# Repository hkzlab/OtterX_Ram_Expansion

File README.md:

# OtterX RAM Expansion

## Introduction

This card expands the RAM of your [OtterX](https://www.tindie.com/products/wavicle/otterx-8-bit-retro-computer/) (a DIY CommanderX16 compatible) computer to 2MB!

Once You switch [J27](https://github.com/RetroRemake/OtterX_Assembly/blob/main/OtterX%20Schematics.pdf) to enable the external RAM and install this board, the computer will automatically detect the 2MB.

### Disclaimer

I take NO responsibility for what happens if you decide to build and use this card. Your computer might crash, catch fire or be destroyed in other nasty ways.
You're encourauged to take what you deem fit from this, and use it in your projects!

## Known Issues

### Rev. 0

- None

## Bill of Materials

| Component         | Qty | Type / Value           | Link                                                     |
| ----------------- | --- | ---------------------- | -------------------------------------------------------- |
| C1, C2, C3, C4    |  4  | 100nF / 1206 / ceramic | https://www.mouser.it/ProductDetail/581-1206YC104JAT2A   |
| U4                |  1  | 74AC139 / SOIC-16      | https://www.mouser.it/ProductDetail/863-MC74AC139DR2G    |
| U1, U2, U3        |  3  | 512Kx8 SRAM / SOP-32   | https://www.mouser.it/ProductDetail/968-R1LP0408DSP5SIS1 |
| J1                |  1  | 2x20 header, 2mm pitch | https://www.mouser.it/ProductDetail/200-MTMM12004TD157 or https://www.mouser.it/ProductDetail/200-MTMM12009LD350 |

Depending on whether you added or not a socket for the IC in the area where the expansion is installed, select one type of header or the other: `MTMM-120-09-L-D-350` clears the height for the sockets and the ICs.

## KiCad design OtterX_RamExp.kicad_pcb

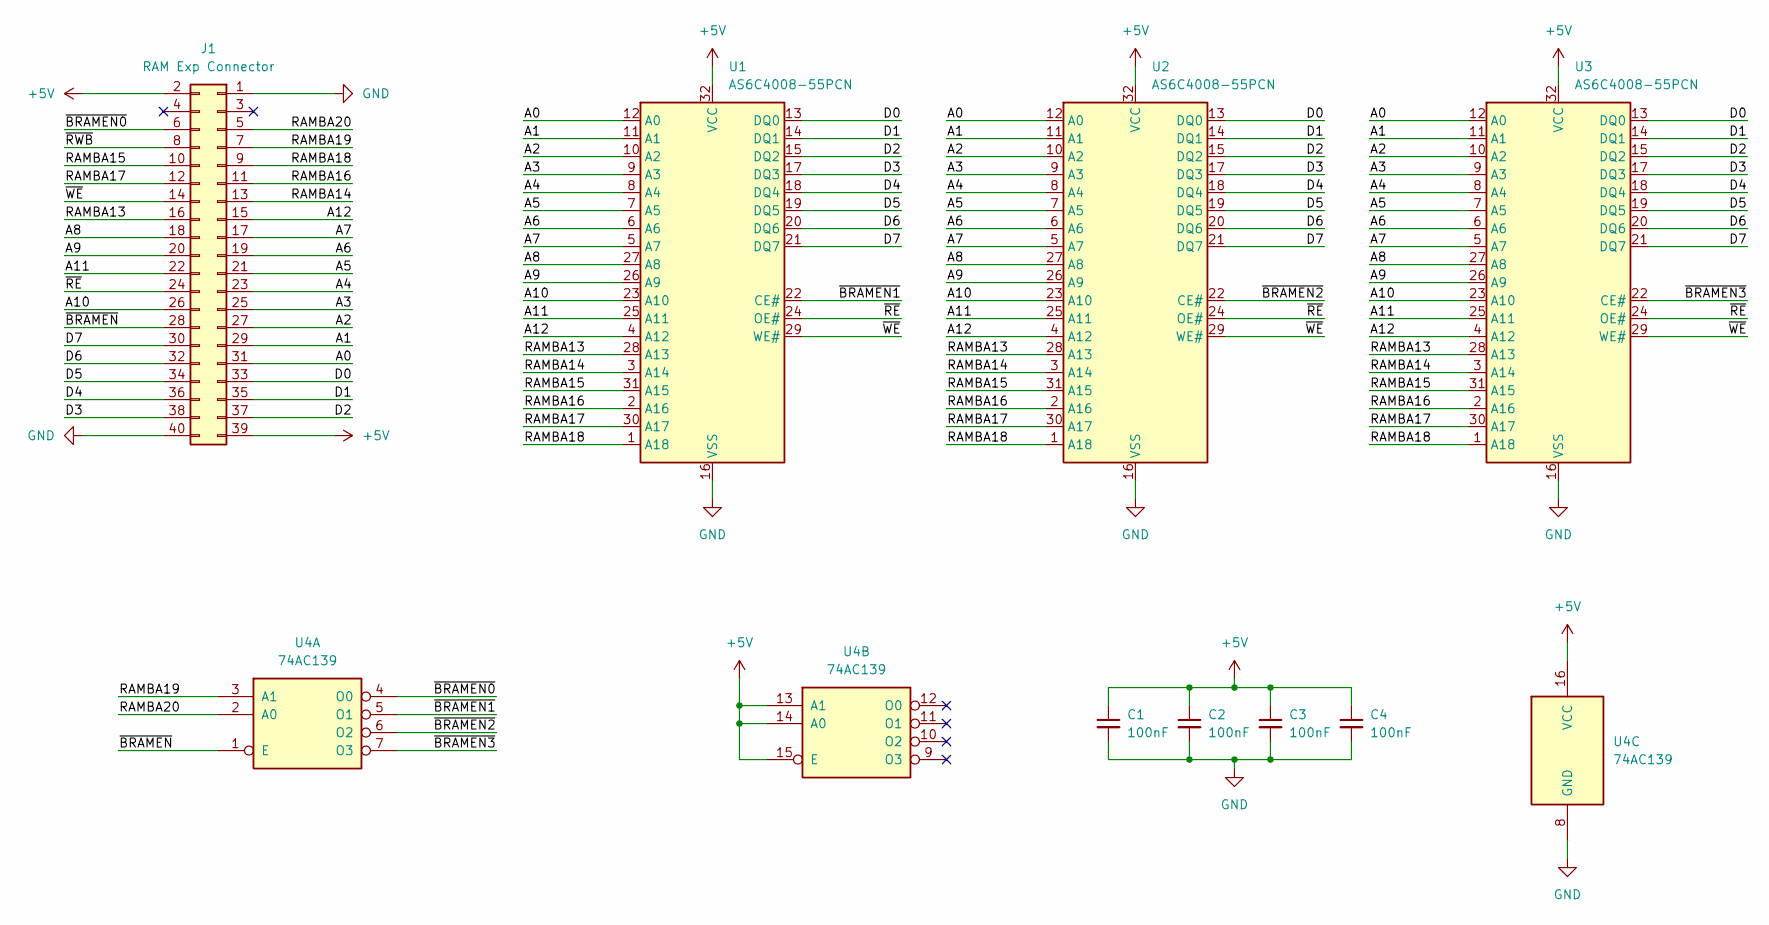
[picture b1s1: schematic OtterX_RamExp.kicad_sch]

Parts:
C1, C2, C3, C4: 100nF; C_1206_3216Metric_Pad1.33x1.80mm_HandSolder
J1: RAM Exp Connector; PinHeader_2x20_P2.00mm_Vertical
U1, U2, U3: AS6C4008-55PCN; SSOP-32_11.305x20.495mm_P1.27mm
U4: 74AC139; SO-16_3.9x9.9mm_P1.27mm

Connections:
+5V: C1.1, C2.1, C3.1, C4.1, J1.2, J1.39, U1.32 (VCC), U2.32 (VCC), U3.32 (VCC), U4.13 (A1), U4.14 (A0), U4.15 (E), U4.16 (VCC)
/A0: J1.31, U1.12 (A0), U2.12 (A0), U3.12 (A0)
/A1: J1.29, U1.11 (A1), U2.11 (A1), U3.11 (A1)
/A2: J1.27, U1.10 (A2), U2.10 (A2), U3.10 (A2)
/A3: J1.25, U1.9 (A3), U2.9 (A3), U3.9 (A3)
/A4: J1.23, U1.8 (A4), U2.8 (A4), U3.8 (A4)
/A5: J1.21, U1.7 (A5), U2.7 (A5), U3.7 (A5)
/A6: J1.19, U1.6 (A6), U2.6 (A6), U3.6 (A6)
/A7: J1.17, U1.5 (A7), U2.5 (A7), U3.5 (A7)
/A8: J1.18, U1.27 (A8), U2.27 (A8), U3.27 (A8)
/A9: J1.20, U1.26 (A9), U2.26 (A9), U3.26 (A9)
/A10: J1.26, U1.23 (A10), U2.23 (A10), U3.23 (A10)
/A11: J1.22, U1.25 (A11), U2.25 (A11), U3.25 (A11)
/A12: J1.15, U1.4 (A12), U2.4 (A12), U3.4 (A12)
/D0: J1.33, U1.13 (DQ0), U2.13 (DQ0), U3.13 (DQ0)
/D1: J1.35, U1.14 (DQ1), U2.14 (DQ1), U3.14 (DQ1)
/D2: J1.37, U1.15 (DQ2), U2.15 (DQ2), U3.15 (DQ2)
/D3: J1.38, U1.17 (DQ3), U2.17 (DQ3), U3.17 (DQ3)
/D4: J1.36, U1.18 (DQ4), U2.18 (DQ4), U3.18 (DQ4)
/D5: J1.34, U1.19 (DQ5), U2.19 (DQ5), U3.19 (DQ5)
/D6: J1.32, U1.20 (DQ6), U2.20 (DQ6), U3.20 (DQ6)
/D7: J1.30, U1.21 (DQ7), U2.21 (DQ7), U3.21 (DQ7)
/RAMBA13: J1.16, U1.28 (A13), U2.28 (A13), U3.28 (A13)
/RAMBA14: J1.13, U1.3 (A14), U2.3 (A14), U3.3 (A14)
/RAMBA15: J1.10, U1.31 (A15), U2.31 (A15), U3.31 (A15)
/RAMBA16: J1.11, U1.2 (A16), U2.2 (A16), U3.2 (A16)
/RAMBA17: J1.12, U1.30 (A17), U2.30 (A17), U3.30 (A17)
/RAMBA18: J1.9, U1.1 (A18), U2.1 (A18), U3.1 (A18)
/RAMBA19: J1.7, U4.3 (A1)
/RAMBA20: J1.5, U4.2 (A0)
/~BRAMEN0: J1.6, U4.4 (O0)
/~BRAMEN1: U1.22 (CE#), U4.5 (O1)
/~BRAMEN2: U2.22 (CE#), U4.6 (O2)
/~BRAMEN3: U3.22 (CE#), U4.7 (O3)
/~BRAMEN: J1.28, U4.1 (E)
/~RE: J1.24, U1.24 (OE#), U2.24 (OE#), U3.24 (OE#)
/~RWB: J1.8
/~WE: J1.14, U1.29 (WE#), U2.29 (WE#), U3.29 (WE#)
GND: C1.2, C2.2, C3.2, C4.2, J1.1, J1.40, U1.16 (VSS), U2.16 (VSS), U3.16 (VSS), U4.8 (GND)

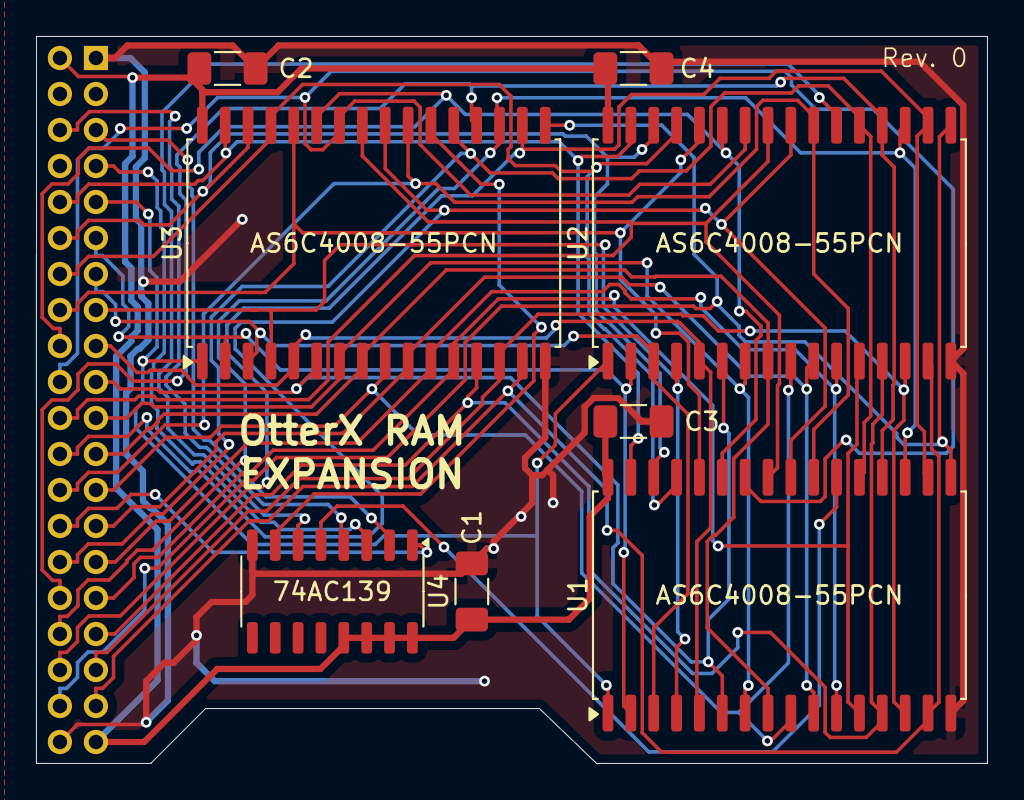
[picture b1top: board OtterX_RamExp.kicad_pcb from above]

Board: 2 copper layers, 52.8 x 40.4 mm, 9 parts (1 on the bottom side), 38 nets.

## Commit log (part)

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2024-05-20 Add ram expansion PCB
2024-05-20 Update the PCB
2024-05-27 Add revision silkscreen
2024-05-27 Added gerber
2024-06-06 Filled in the README, added schematics
2024-06-06 Resized the pic
2024-06-06 Change some wording in the readme
2024-06-06 You actually switch the jumper first...
2024-06-06 Typo
